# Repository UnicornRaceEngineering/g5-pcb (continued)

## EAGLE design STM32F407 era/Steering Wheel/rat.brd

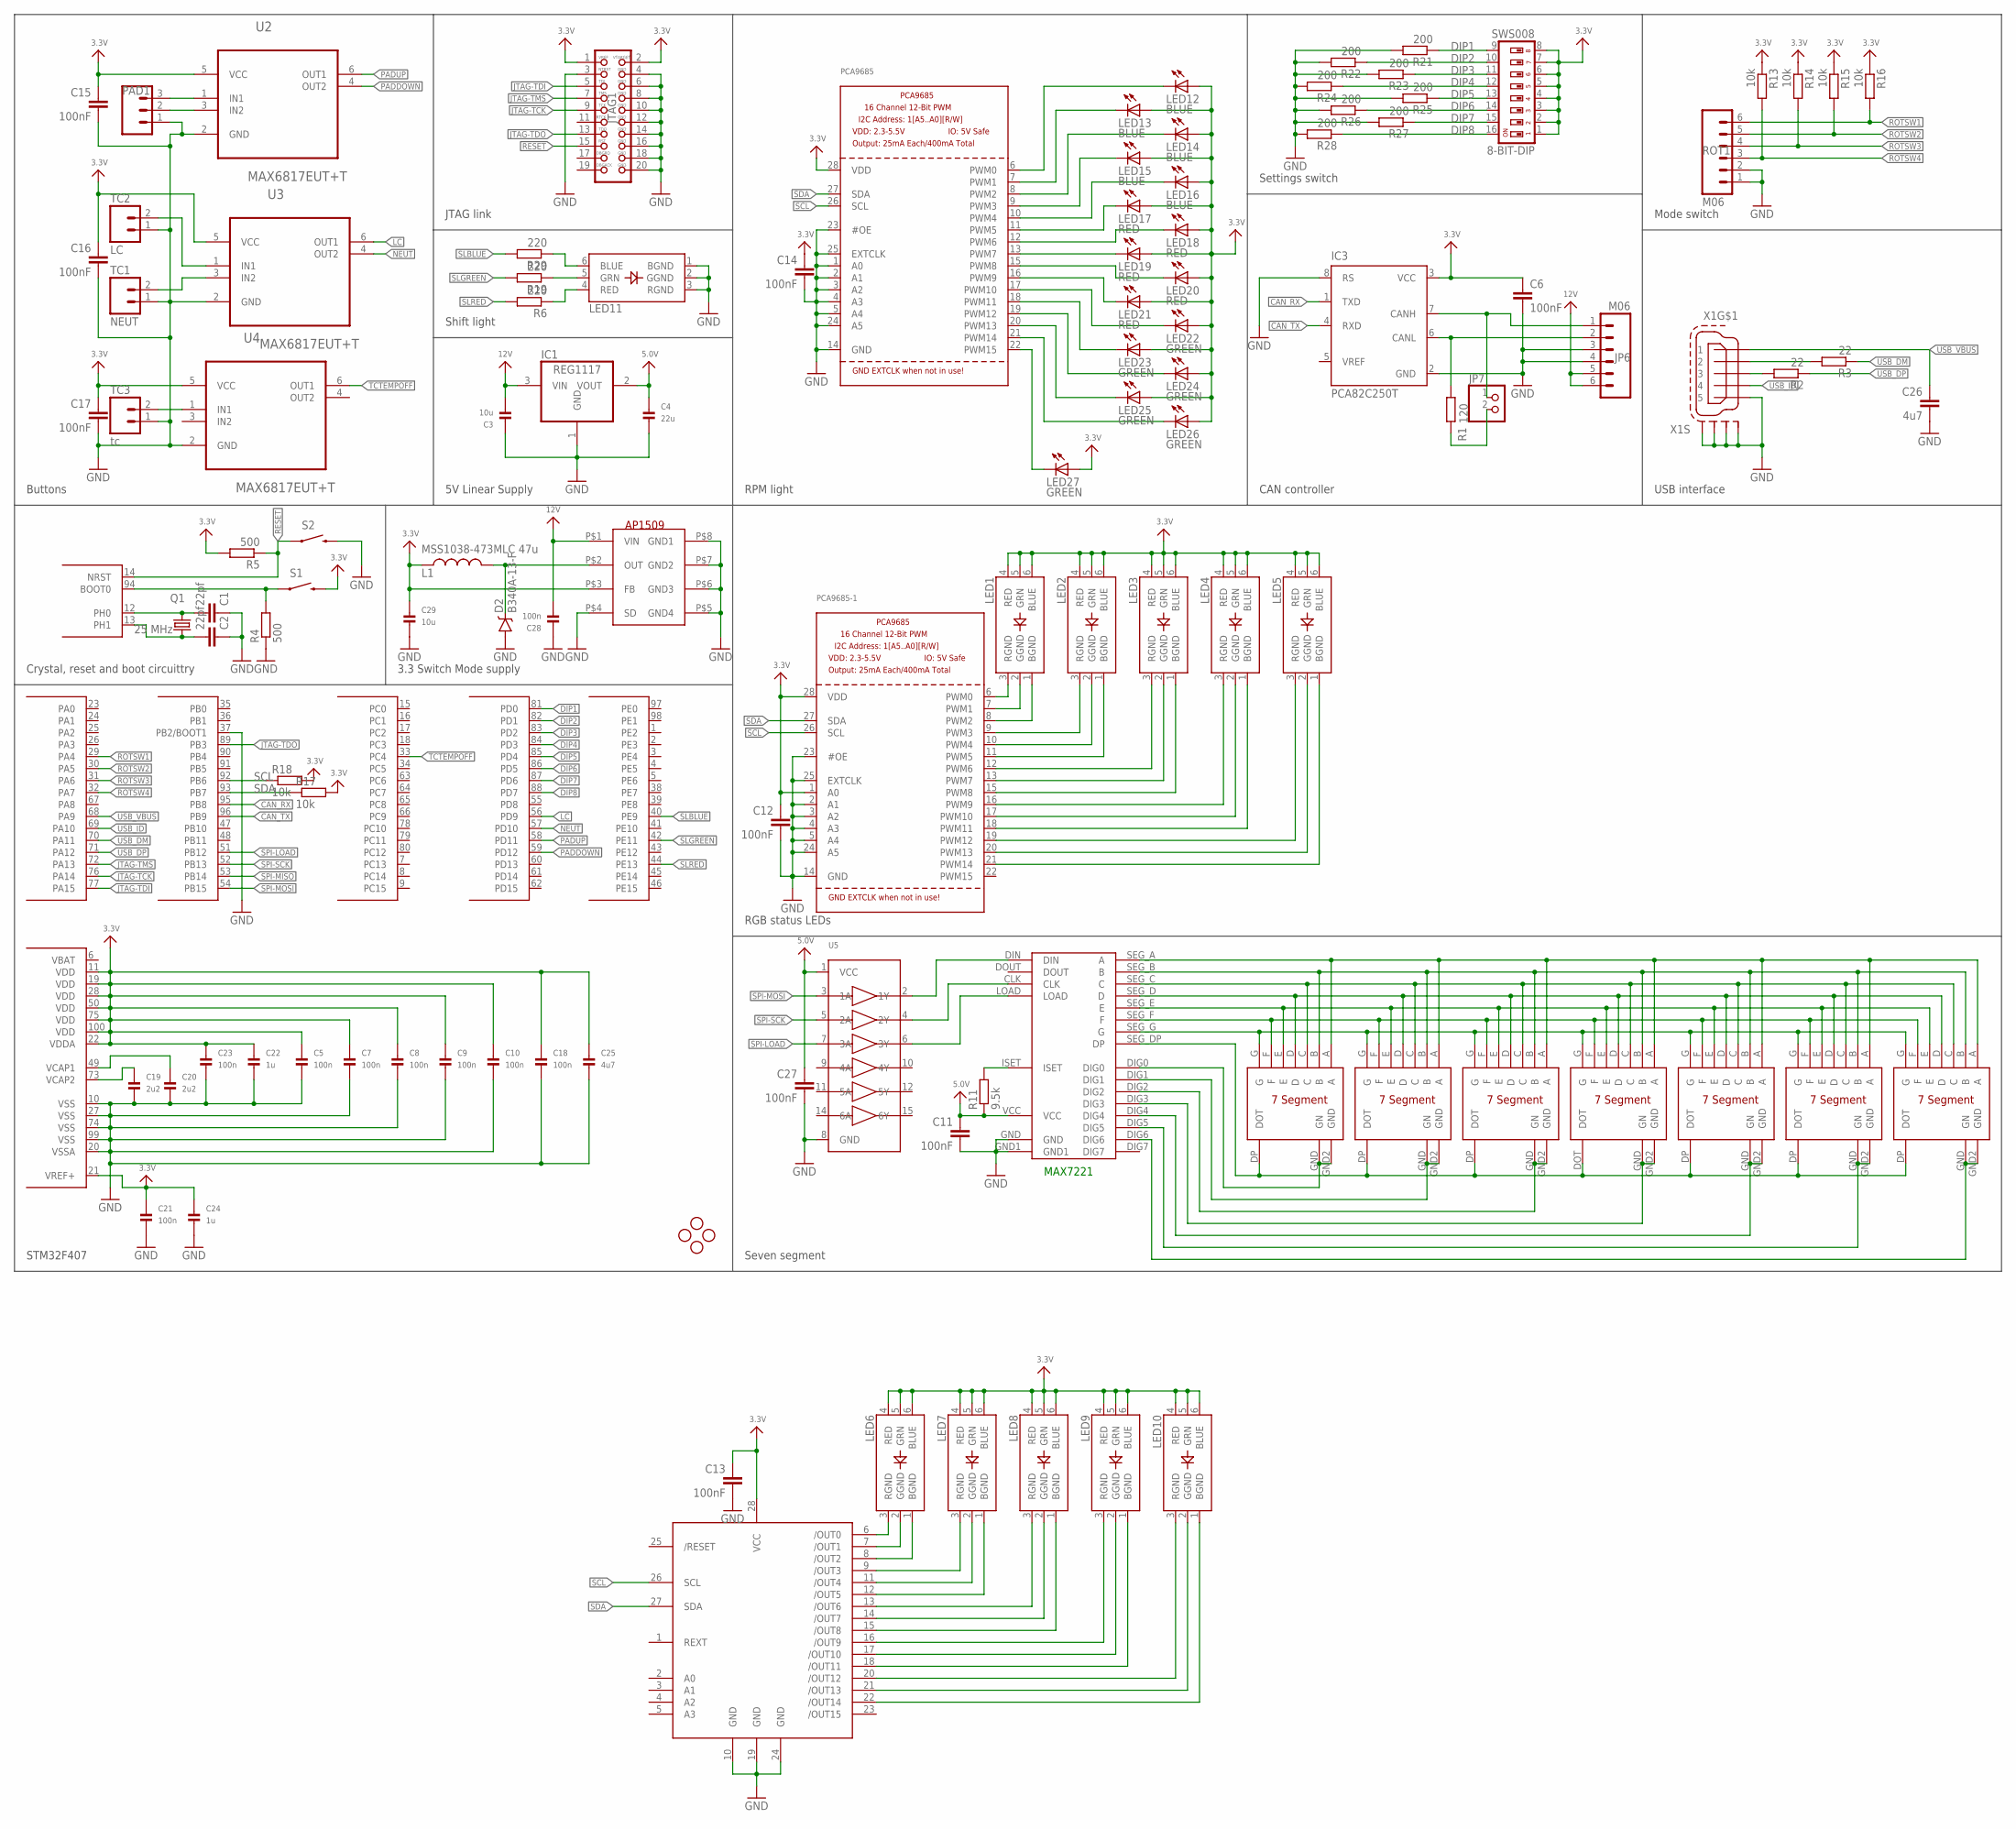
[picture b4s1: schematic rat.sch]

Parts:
8-BIT-DIP: SWS008; SMS-008
C1, C2: 22pf; C0603K
C3, C29: 10u; 0805
C4: 22u; _0603MP
C5, C7, C8, C9, C10, C18, C21, C23: 100n; _0402MP
C6, C11, C12, C13, C14, C15, C16, C17, C27: 100nF; C0603K
C19, C20: 2u2; _0402MP
C22, C24: 1u; _0402MP
C25: 4u7; _0402MP
C26: 4u7; C0603K
C28: 100n; _0603MP
D2: B340A-13-F; SMA-DIODE
IC1: REG1117; SOT223
IC3: PCA82C250T; SO8
JP2, JP3, JP4, JP5: STAND-OFF
JP6: M06; S6B_PH
JP7: PINHD-1X2/90; 1X02/90
JTAG1: JTAG-ARMEDGE; MOLEX20_RIGHTANGLE
L1: MSS1038-473MLC 47u; CDRH125
LED1, LED2, LED3, LED4, LED5, LED6, LED7, LED8, LED9, LED10, LED11: LED_RGB_PLCC6CREE-CLV6A; RGBLED_PLCC6
LED12, LED13, LED14, LED15, LED16: BLUE; 1206
LED17, LED18, LED19, LED20, LED21: RED; 1206
LED22, LED23, LED24, LED25, LED26, LED27: GREEN; 1206
MAX7221: MAX7221-SMD; MAX7221
PAD1: M03; S3B-PH
PCA9685, PCA9685-1: PCA9685; TSSOP28
Q1: 25 MHz; HC49U70
R1: 120; R0603
R2, R3: 22; R0603
R4, R5: 500; R0603
R6, R19, R29: 220; R0603
R11: 9.5k; R0603
R13, R14, R15, R16, R17, R18: 10k; R0603
R21, R22, R23, R24, R25, R26, R27, R28: 200; R0603
ROT1: M06; S6B_PH
S1, S2: SWITCH-MOMENTARY-2-SMD-1101NE; TACTILE-SWITCH-1101NE
TC1: NEUT; S2B-PH
TC2: LC; S2B-PH
TC3: tc; S2B-PH
U1: STM32F4-100; SQFP-S-14X14-100
U2, U3, U4: MAX6817EUT+T; SOT95P280X145-6N
U5: 74HC4050D; SOIC16
U$2, U$3, U$4, U$6, U$7, U$8: REDSEVENSEGMENT; REDSEGMENT
U$5: BIGSEVENSEGMENT
U$10: AP1509; SOP-8L
U$38: TLC59116; TSSOP28
X1: MINI-USB-SCHIELD-32005-201; 32005-201

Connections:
3.3V: 8-BIT-DIP.1, 8-BIT-DIP.2, 8-BIT-DIP.3, 8-BIT-DIP.4, 8-BIT-DIP.5, 8-BIT-DIP.6, 8-BIT-DIP.7, 8-BIT-DIP.8, C5.1, C6.1, C7.1, C8.1, C9.1, C10.1, C12.1, C13.1, C14.1, C15.1, C16.1, C17.1, C18.1, C21.1, C22.1, C23.1, C24.1, C25.1, C29.1, IC3.3 (VCC), JTAG1.1, JTAG1.2, L1.1, LED1.4 (RED), LED1.5 (GRN), LED1.6 (BLUE), LED2.4 (RED), LED2.5 (GRN), LED2.6 (BLUE), LED3.4 (RED), LED3.5 (GRN), LED3.6 (BLUE), LED4.4 (RED), LED4.5 (GRN), LED4.6 (BLUE), LED5.4 (RED), LED5.5 (GRN), LED5.6 (BLUE), LED6.4 (RED), LED6.5 (GRN), LED6.6 (BLUE), LED7.4 (RED), LED7.5 (GRN), LED7.6 (BLUE), LED8.4 (RED), LED8.5 (GRN), LED8.6 (BLUE), LED9.4 (RED), LED9.5 (GRN), LED9.6 (BLUE), LED10.4 (RED), LED10.5 (GRN), LED10.6 (BLUE), LED12.A, LED13.A, LED14.A, LED15.A, LED16.A, LED17.A, LED18.A, LED19.A, LED20.A, LED21.A, LED22.A, LED23.A, LED24.A, LED25.A, LED26.A, LED27.A, PCA9685.28 (VDD), PCA9685-1.1 (A0), PCA9685-1.28 (VDD), R5.2, R13.1, R14.1, R15.1, R16.1, R17.2, R18.2, S1.P$2 (2), U1.11 (VDD), U1.19 (VDD), U1.21 (VREF+), U1.22 (VDDA), U1.28 (VDD), U1.50 (VDD), U1.75 (VDD), U1.100 (VDD), U2.5 (VCC), U3.5 (VCC), U4.5 (VCC), U$10.P$3 (FB), U$38.28 (VCC)
5.0V: C4.1, C11.1, C27.1, IC1.2 (VOUT), MAX7221.VCC, R11.1, U5.1 (VCC)
12V: C3.2, C28.2, IC1.3 (VIN), JP6.5, JP6.6, U$10.P$1 (VIN)
CANJUMP1: IC3.7 (CANH), JP6.1, JP7.1
CANJUMP2: JP7.2, R1.2
CAN_RX: IC3.1 (TXD), U1.95 (PB8)
CAN_TX: IC3.4 (RXD), U1.96 (PB9)
DIP1: 8-BIT-DIP.9, R21.1, U1.81 (PD0)
DIP2: 8-BIT-DIP.10, R22.1, U1.82 (PD1)
DIP3: 8-BIT-DIP.11, R23.1, U1.83 (PD2)
DIP4: 8-BIT-DIP.12, R24.1, U1.84 (PD3)
DIP5: 8-BIT-DIP.13, R25.1, U1.85 (PD4)
DIP6: 8-BIT-DIP.14, R26.1, U1.86 (PD5)
DIP7: 8-BIT-DIP.15, R27.1, U1.87 (PD6)
DIP8: 8-BIT-DIP.16, R28.1, U1.88 (PD7)
GND: C1.1, C2.1, C3.1, C4.2, C5.2, C6.2, C7.2, C8.2, C9.2, C10.2, C11.2, C12.2, C13.2, C14.2, C15.2, C16.2, C17.2, C18.2, C19.2, C20.2, C21.2, C22.2, C23.2, C24.2, C25.2, C26.2, C27.2, C28.1, C29.2, D2.A, IC1.1 (GND), IC3.2 (GND), IC3.8 (RS), JP6.3, JP6.4, JTAG1.3, JTAG1.4, JTAG1.6, JTAG1.8, JTAG1.10, JTAG1.12, JTAG1.14, JTAG1.16, JTAG1.18, JTAG1.20, LED11.1 (BGND), LED11.2 (GGND), LED11.3 (RGND), MAX7221.GND, MAX7221.GND1, PAD1.1, PCA9685.1 (A0), PCA9685.2 (A1), PCA9685.3 (A2), PCA9685.4 (A3), PCA9685.5 (A4), PCA9685.14 (GND), PCA9685.23 (#OE), PCA9685.24 (A5), PCA9685.25 (EXTCLK), PCA9685-1.2 (A1), PCA9685-1.3 (A2), PCA9685-1.4 (A3), PCA9685-1.5 (A4), PCA9685-1.14 (GND), PCA9685-1.23 (#OE), PCA9685-1.24 (A5), PCA9685-1.25 (EXTCLK), R4.1, R21.2, R22.2, R23.2, R24.2, R25.2, R26.2, R27.2, R28.2, ROT1.1, ROT1.2, S2.P$2 (2), TC1.1, TC2.1, TC3.1, U1.10 (VSS), U1.20 (VSSA), U1.27 (VSS), U1.37 (PB2/BOOT1), U1.74 (VSS), U1.99 (VSS), U2.2 (GND), U3.2 (GND), U4.2 (GND), U5.8 (GND), U$10.P$4 (SD), U$10.P$5 (GND4), U$10.P$6 (GND3), U$10.P$7 (GND2), U$10.P$8 (GND1), U$38.10 (GND), U$38.19 (GND), U$38.24 (GND), X1.5, X1.M1 (S1), X1.M2 (S2), X1.M3 (S3), X1.M4 (S4)
JTAG-TCK: JTAG1.9, U1.76 (PA14)
JTAG-TDI: JTAG1.5, U1.77 (PA15)
JTAG-TDO: JTAG1.13, U1.89 (PB3)
JTAG-TMS: JTAG1.7, U1.72 (PA13)
LC: U1.56 (PD9), U3.6 (OUT1)
unnamed: C2.2, Q1.1, U1.13 (PH1)
unnamed: C1.2, Q1.2, U1.12 (PH0)
unnamed: MAX7221.SEG_A (A), U$2.A, U$3.A, U$4.A, U$5.A, U$6.A, U$7.A, U$8.A
unnamed: MAX7221.CLK, U5.4 (2Y)
unnamed: MAX7221.LOAD, U5.6 (3Y)
unnamed: MAX7221.SEG_B (B), U$2.B, U$3.B, U$4.B, U$5.B, U$6.B, U$7.B, U$8.B
unnamed: MAX7221.DIN, U5.2 (1Y)
unnamed: MAX7221.SEG_C (C), U$2.C, U$3.C, U$4.C, U$5.C, U$6.C, U$7.C, U$8.C
unnamed: LED13.C, PCA9685.7 (PWM1)
unnamed: C19.1, U1.73 (VCAP2)
unnamed: LED14.C, PCA9685.8 (PWM2)
unnamed: MAX7221.SEG_D (D), U$2.D, U$3.D, U$4.D, U$5.D, U$6.D, U$7.D, U$8.D
unnamed: MAX7221.SEG_E (E), U$2.E, U$3.E, U$4.E, U$5.E, U$6.E, U$7.E, U$8.E
unnamed: MAX7221.SEG_F (F), U$2.F, U$3.F, U$4.F, U$5.F, U$6.F, U$7.F, U$8.F
unnamed: MAX7221.SEG_G (G), U$2.G, U$3.G, U$4.G, U$5.G, U$6.G, U$7.G, U$8.G
unnamed: MAX7221.DIG0, U$2.GND (GN), U$2.GND2 (GND)
unnamed: MAX7221.DIG1, U$3.GND (GN), U$3.GND2 (GND)
unnamed: MAX7221.DIG2, U$4.GND (GN), U$4.GND2 (GND)
unnamed: MAX7221.DIG3, U$5.GND (GN), U$5.GND2 (GND)
unnamed: MAX7221.DIG4, U$6.GND (GN), U$6.GND2 (GND)
unnamed: MAX7221.DIG5, U$7.GND (GN), U$7.GND2 (GND)
unnamed: MAX7221.DIG6, U$8.GND (GN), U$8.GND2 (GND)
unnamed: LED15.C, PCA9685.9 (PWM3)
unnamed: C20.1, U1.49 (VCAP1)
unnamed: MAX7221.SEG_DP (DP), U$2.DP (DOT), U$3.DP (DOT), U$4.DP (DOT), U$5.DOT, U$6.DP (DOT), U$7.DP (DOT), U$8.DP (DOT)
unnamed: R2.2, X1.3
unnamed: MAX7221.ISET, R11.2
unnamed: R3.2, X1.2
unnamed: LED11.5 (GRN), R19.1
unnamed: R4.2, S1.P$1 (1), U1.94 (BOOT0)
unnamed: LED11.6 (BLUE), R29.1
unnamed: LED11.4 (RED), R6.1
unnamed: LED16.C, PCA9685.10 (PWM4)
unnamed: LED17.C, PCA9685.11 (PWM5)
unnamed: LED18.C, PCA9685.12 (PWM6)
unnamed: LED19.C, PCA9685.13 (PWM7)
unnamed: LED20.C, PCA9685.15 (PWM8)
unnamed: LED21.C, PCA9685.16 (PWM9)
unnamed: LED22.C, PCA9685.17 (PWM10)
unnamed: LED23.C, PCA9685.18 (PWM11)
unnamed: LED24.C, PCA9685.19 (PWM12)
unnamed: LED25.C, PCA9685.20 (PWM13)
unnamed: LED26.C, PCA9685.21 (PWM14)
unnamed: LED1.3 (RGND), PCA9685-1.6 (PWM0)
unnamed: D2.C, L1.2, U$10.P$2 (OUT)
unnamed: LED1.2 (GGND), PCA9685-1.7 (PWM1)
unnamed: LED1.1 (BGND), PCA9685-1.8 (PWM2)
unnamed: LED2.3 (RGND), PCA9685-1.9 (PWM3)
unnamed: IC3.6 (CANL), JP6.2, R1.1
unnamed: LED2.2 (GGND), PCA9685-1.10 (PWM4)
unnamed: LED2.1 (BGND), PCA9685-1.11 (PWM5)
unnamed: LED3.3 (RGND), PCA9685-1.12 (PWM6)
unnamed: LED3.2 (GGND), PCA9685-1.13 (PWM7)
unnamed: LED3.1 (BGND), PCA9685-1.15 (PWM8)
unnamed: LED4.3 (RGND), PCA9685-1.16 (PWM9)
unnamed: LED12.C, PCA9685.6 (PWM0)
unnamed: LED4.2 (GGND), PCA9685-1.17 (PWM10)
unnamed: LED4.1 (BGND), PCA9685-1.18 (PWM11)
unnamed: LED5.3 (RGND), PCA9685-1.19 (PWM12)
unnamed: LED5.2 (GGND), PCA9685-1.20 (PWM13)
unnamed: LED5.1 (BGND), PCA9685-1.21 (PWM14)
unnamed: LED6.3 (RGND), U$38.6 (/OUT0)
unnamed: LED6.2 (GGND), U$38.7 (/OUT1)
unnamed: LED6.1 (BGND), U$38.8 (/OUT2)
unnamed: LED7.3 (RGND), U$38.9 (/OUT3)
unnamed: LED7.2 (GGND), U$38.11 (/OUT4)
unnamed: LED7.1 (BGND), U$38.12 (/OUT5)
unnamed: LED8.3 (RGND), U$38.13 (/OUT6)
unnamed: LED8.2 (GGND), U$38.14 (/OUT7)
unnamed: LED8.1 (BGND), U$38.15 (/OUT8)
unnamed: LED9.3 (RGND), U$38.16 (/OUT9)
unnamed: LED9.2 (GGND), U$38.17 (/OUT10)
unnamed: LED9.1 (BGND), U$38.18 (/OUT11)
unnamed: LED10.3 (RGND), U$38.20 (/OUT12)
unnamed: LED10.2 (GGND), U$38.21 (/OUT13)
unnamed: LED10.1 (BGND), U$38.22 (/OUT14)
unnamed: LED27.C, PCA9685.22 (PWM15)
unnamed: TC1.2, U3.3 (IN2)
unnamed: PAD1.3, U2.1 (IN1)
unnamed: PAD1.2, U2.3 (IN2)
unnamed: TC2.2, U3.1 (IN1)
unnamed: TC3.2, U4.1 (IN1)
NEUT: U1.57 (PD10), U3.4 (OUT2)
PADDOWN: U1.59 (PD12), U2.4 (OUT2)
PADUP: U1.58 (PD11), U2.6 (OUT1)
RESET: JTAG1.15, R5.1, S2.P$1 (1), U1.14 (NRST)
ROTSW1: R16.2, ROT1.6, U1.29 (PA4)
ROTSW2: R15.2, ROT1.5, U1.30 (PA5)
ROTSW3: R14.2, ROT1.4, U1.31 (PA6)
ROTSW4: R13.2, ROT1.3, U1.32 (PA7)
SCL: PCA9685.26 (SCL), PCA9685-1.26 (SCL), R18.1, U1.92 (PB6), U$38.26 (SCL)
SDA: PCA9685.27 (SDA), PCA9685-1.27 (SDA), R17.1, U1.93 (PB7), U$38.27 (SDA)
SLBLUE: R29.2, U1.40 (PE9)
SLGREEN: R19.2, U1.42 (PE11)
SLRED: R6.2, U1.44 (PE13)
SPI-LOAD: U1.51 (PB12), U5.7 (3A)
SPI-MISO: U1.53 (PB14)
SPI-MOSI: U1.54 (PB15), U5.3 (1A)
SPI-SCK: U1.52 (PB13), U5.5 (2A)
TCTEMPOFF: U1.33 (PC4), U4.6 (OUT1)
USB_DM: R3.1, U1.70 (PA11)
USB_DP: R2.1, U1.71 (PA12)
USB_ID: U1.69 (PA10), X1.4
USB_VBUS: C26.1, U1.68 (PA9), X1.1
VBAT: U1.6 (VBAT)

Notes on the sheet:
MAX7221
RPM light
CAN controller
RGB status LEDs
Seven segment
USB interface
Mode switch
Settings switch
JTAG link
Shift light
STM32F407
5V Linear Supply
3.3 Switch Mode supply
Crystal, reset and boot circuittry
Buttons

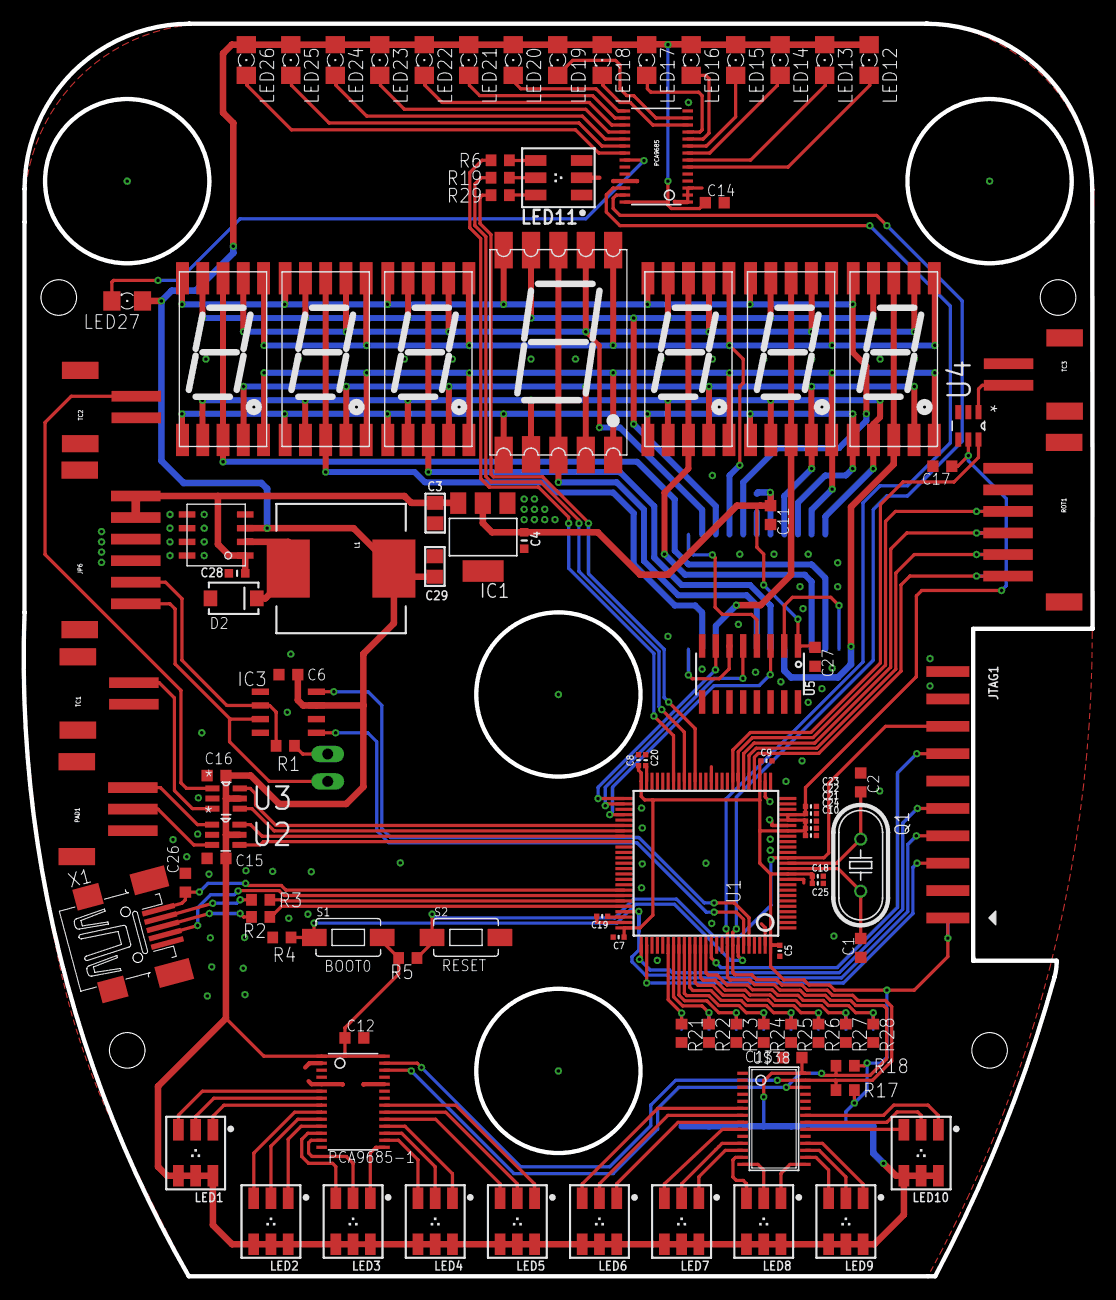
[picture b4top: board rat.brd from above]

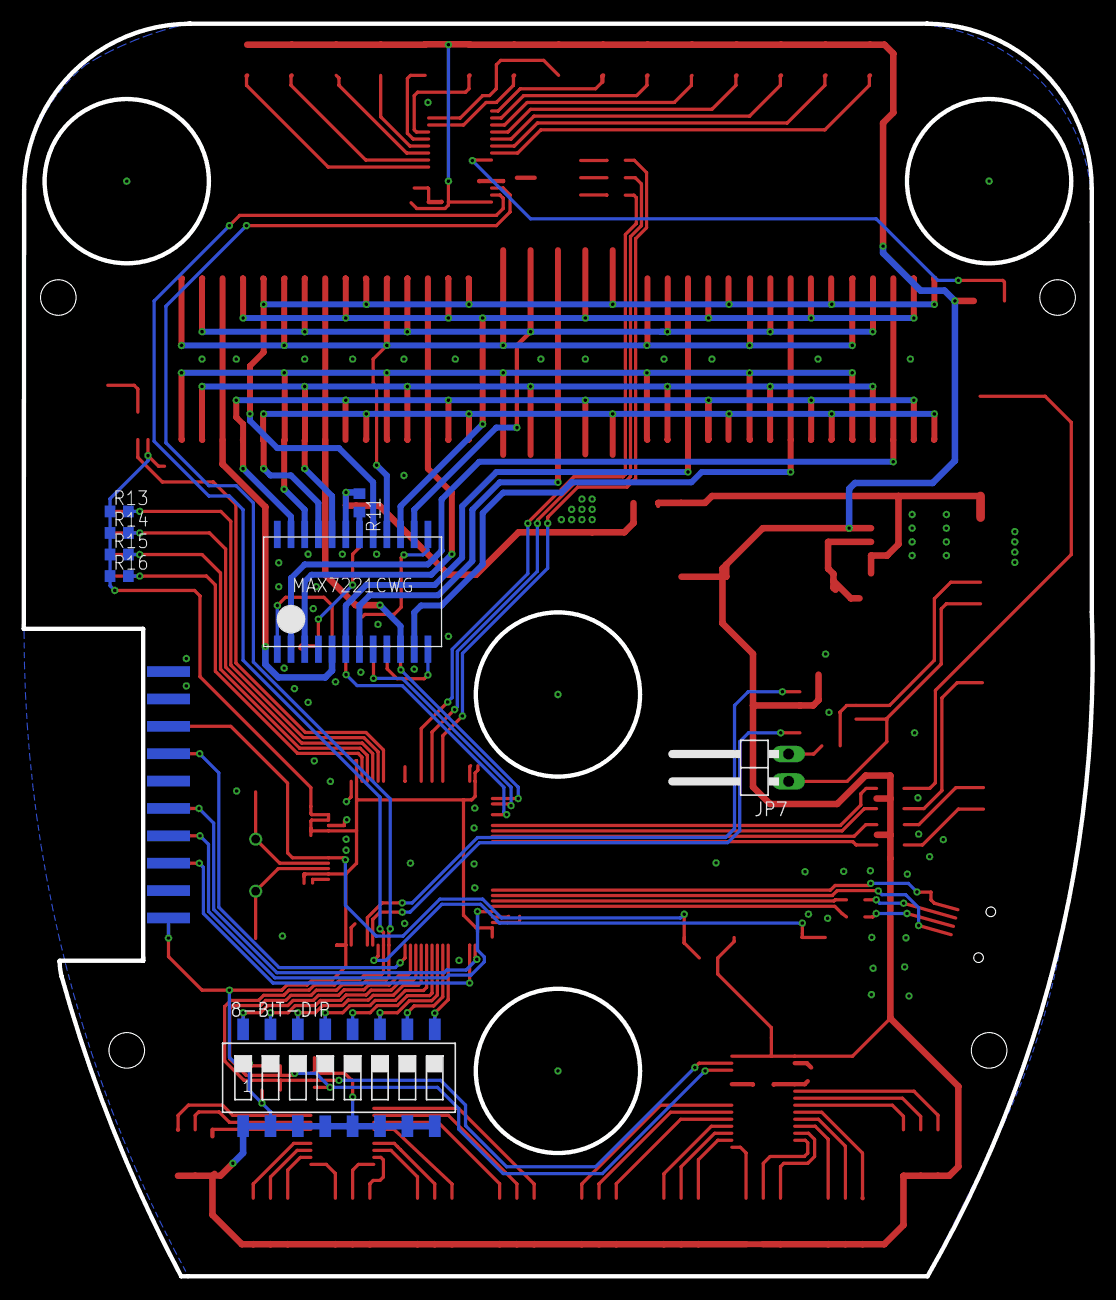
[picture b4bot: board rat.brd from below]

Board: 2 copper layers, 99.2 x 116.2 mm, 117 parts (8 on the bottom side), 124 nets.
